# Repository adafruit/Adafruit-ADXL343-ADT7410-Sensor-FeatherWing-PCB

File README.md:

## Adafruit ADXL343 + ADT7410 Sensor FeatherWing PCB

<a href="http://www.adafruit.com/products/4147"><br/>
Click here to purchase one from the Adafruit shop</a>

PCB files for the Adafruit ADXL343 + ADT7410 Sensor FeatherWing. 

Format is EagleCAD schematic and board layout
* https://www.adafruit.com/product/4147

### Description

Upgrade any Feather board with motion and precision temperature sensing, with this all-in-one sensing FeatherWing. It sports two fantastic sensors from Analog Devices: an ADXL343 triple-axis accelerometer and an ADT7410 precision temperature sensor.

Both sensors are connected over the shared I2C bus, so you can use it with any and all Feathers! We also break out the interrupt pins and address-selection jumpers in case you want multiple Feathers or have I2C address conflicts. We've got both Arduino (C/C++) and CircuitPython libraries available so you can use it with any Feather board and get data readings in under 5 minutes.

The Analog Devices ADXL343 has three axes of measurements, X Y Z. You can set the sensitivity level to either +-2g, +-4g, +-8g or +-16g. The lower range gives more resolution for slow movements, the higher range is good for high speed tracking. The ADXL343 is the latest and greatest from Analog Devices, known for their exceptional quality MEMS devices.

The Analog Devices ADT7410 is an I2C temperature sensor, with 16-bit 0.0078°C temperature resolution and 0.5°C temperature tolerance. Use with any microcontroller to get reliable temperature readings with ease.

Thanks to Digi-Key and Analog Devices for sponsoring the development of this breakout board - we've made the PCB "Digi-Key red" in their honor!

### License

Adafruit invests time and resources providing this open source design, please support Adafruit and open-source hardware by purchasing products from [Adafruit](https://www.adafruit.com)!

Designed by Limor Fried/Ladyada for Adafruit Industries.

Creative Commons Attribution/Share-Alike, all text above must be included in any redistribution. 
See license.txt for additional details.

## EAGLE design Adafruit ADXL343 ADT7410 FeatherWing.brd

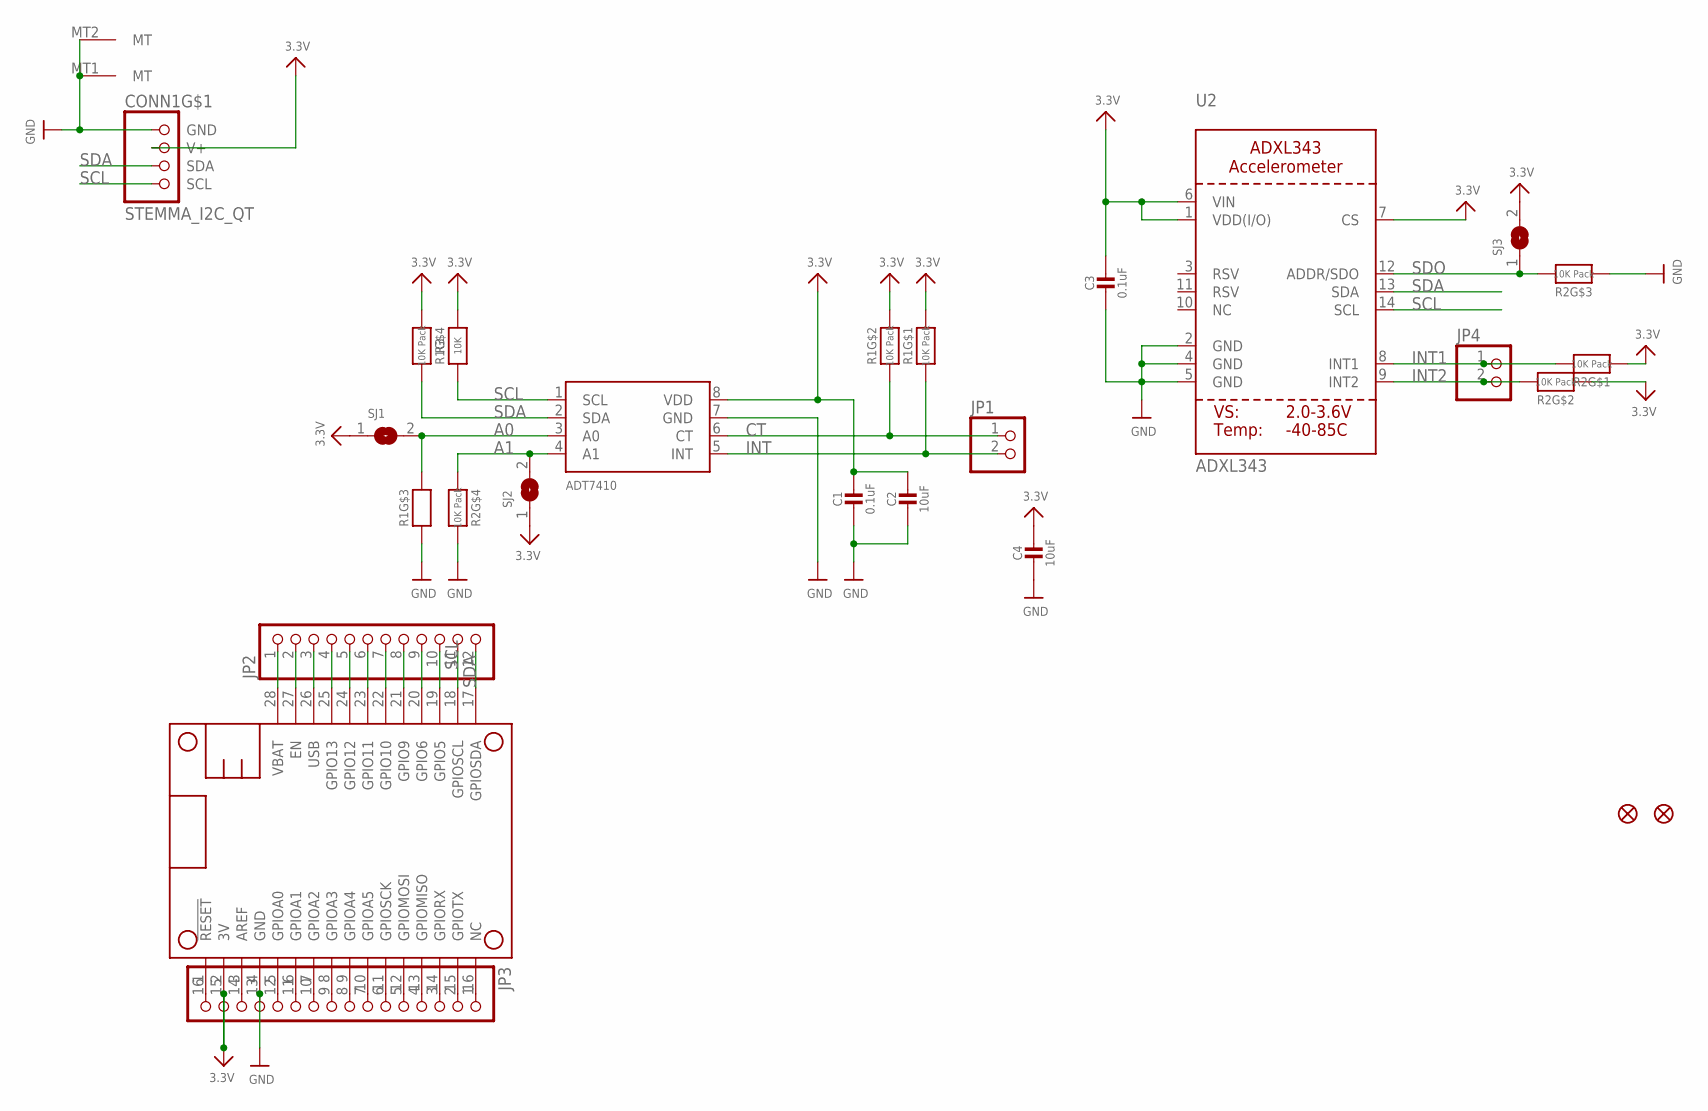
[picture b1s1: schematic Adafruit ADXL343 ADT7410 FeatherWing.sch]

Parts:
C1, C3: 0.1uF; 0603-NO
C2, C4: 10uF; 0805-NO
CONN1: STEMMA_I2C_QT; JST_SH4
FID1, FID2: FIDUCIAL_1MM
JP1, JP4: HEADER-1X2ROUND; 1X02_ROUND
JP2: HEADER-1X1276MIL; 1X12_ROUND_76MIL
JP3: HEADER-1X16_76MIL; 1X16_ROUND_76MIL
MS1: FEATHERWING_NODIM
R1, R2: 10K Pack; RESPACK_4X0603
R3: 10K; 0603-NO
SJ1, SJ2, SJ3: SOLDERJUMPER; SOLDERJUMPER_ARROW_NOPASTE
U1: ADT7410; SOIC8_150MIL
U2: ADXL343; LGA14

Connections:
3.3V: C1.1, C2.1, C3.1, C4.1, CONN1.2 (V+), JP3.15, MS1.2 (3V), R1.4 (1), R1.7 (2), R1.8 (2), R2.1, R2.2 (1), R3.2, SJ1.1, SJ2.1, SJ3.2, U1.8 (VDD), U2.1 (VDD(I/O)), U2.6 (VIN), U2.7 (CS)
A0: R1.6 (2), SJ1.2, U1.3 (A0)
A1: R2.4 (1), SJ2.2, U1.4 (A1)
CT: JP1.1, R1.2 (1), U1.6 (CT)
GND: C1.2, C2.2, C3.2, C4.2, CONN1.1 (GND), CONN1.MT1 (MT), CONN1.MT2 (MT), JP3.13, MS1.4 (GND), R1.3 (1), R2.3 (1), R2.5 (2), U1.7 (GND), U2.2 (GND), U2.4 (GND), U2.5 (GND)
INT: JP1.2, R1.1, U1.5 (INT)
INT1: JP4.1, R2.8 (2), U2.8 (INT1)
INT2: JP4.2, R2.7 (2), U2.9 (INT2)
unnamed: JP2.2, MS1.27 (EN)
unnamed: JP2.4, MS1.25 (GPIO13)
unnamed: JP2.5, MS1.24 (GPIO12)
unnamed: JP2.6, MS1.23 (GPIO11)
unnamed: JP2.7, MS1.22 (GPIO10)
unnamed: JP2.8, MS1.21 (GPIO9)
unnamed: JP2.9, MS1.20 (GPIO6)
unnamed: JP2.10, MS1.19 (GPIO5)
unnamed: JP3.1, MS1.16 (NC)
unnamed: JP3.2, MS1.15 (GPIOTX)
unnamed: JP3.3, MS1.14 (GPIORX)
unnamed: JP3.4, MS1.13 (GPIOMISO)
unnamed: JP3.5, MS1.12 (GPIOMOSI)
unnamed: JP3.6, MS1.11 (GPIOSCK)
unnamed: JP3.7, MS1.10 (GPIOA5)
unnamed: JP3.8, MS1.9 (GPIOA4)
unnamed: JP3.9, MS1.8 (GPIOA3)
unnamed: JP3.10, MS1.7 (GPIOA2)
unnamed: JP3.11, MS1.6 (GPIOA1)
unnamed: JP3.12, MS1.5 (GPIOA0)
unnamed: JP3.14, MS1.3 (AREF)
unnamed: JP3.16, MS1.1 (!RESET)
SCL: CONN1.4 (SCL), JP2.11, MS1.18 (GPIOSCL), R3.1, U1.1 (SCL), U2.14 (SCL)
SDA: CONN1.3 (SDA), JP2.12, MS1.17 (GPIOSDA), R1.5 (2), U1.2 (SDA), U2.13 (SDA)
SDO: R2.6 (2), SJ3.1, U2.12 (ADDR/SDO)
USB: JP2.3, MS1.26 (USB)
VBAT: JP2.1, MS1.28 (VBAT)

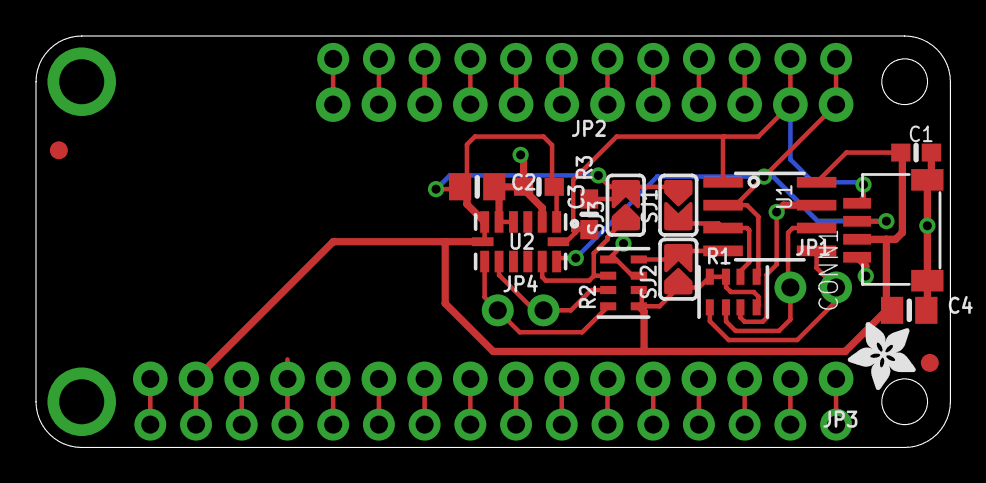
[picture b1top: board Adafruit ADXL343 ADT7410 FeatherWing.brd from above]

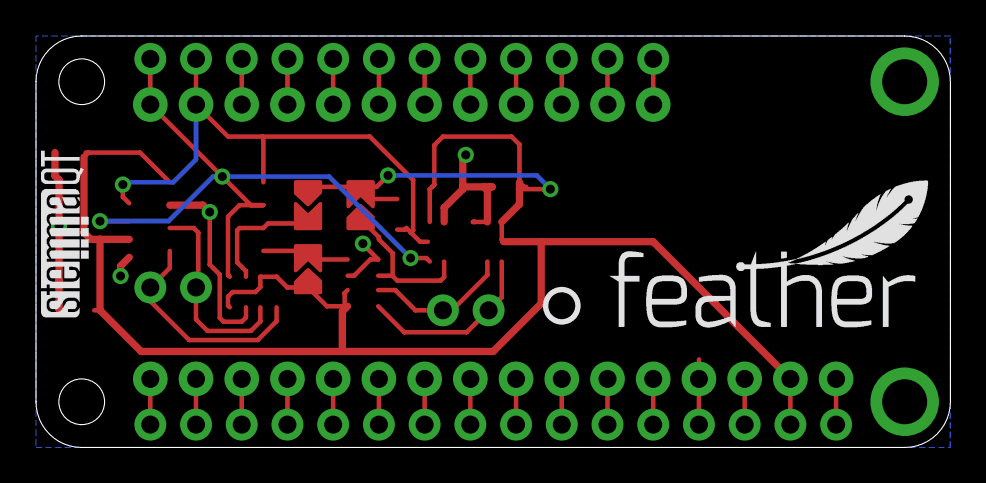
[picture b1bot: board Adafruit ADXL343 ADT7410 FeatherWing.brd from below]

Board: 2 copper layers, 50.8 x 22.9 mm, 25 parts (3 on the bottom side), 35 nets.

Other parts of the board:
U$1: PCBFEAT-REV-040
U$23: FEATHERLOGO_MED
U$24: ADIWING_TOP
U$28: ADAFRUIT_3.5MM
U$29: STEMMAQT

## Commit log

2023-07-31 Add board files.

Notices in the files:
parts and their libraries:
microbuilder: This work is placed in the public domain, and may be freely used for commercial and non-commercial work with the following conditions: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
